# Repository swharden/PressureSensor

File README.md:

# Digital Pressure Sensor

This project contains design files for a minimal complexity digital pressure sensor. It uses a [HX710](https://image.micros.com.pl/_dane_techniczne_auto/uphx710b%20smd.pdf) 24-bit ADC to read differential voltage across a Whetstone bridge pressure sensor, then an [AD64DD32](https://ww1.microchip.com/downloads/aemDocuments/documents/MCU08/ProductDocuments/DataSheets/AVR64DD32-28-Prelim-DataSheet-DS40002315B.pdf) applies signal filtering in software and outputs the result as an analog signal using its built-in DAC. Filtering in software allows filter settings and recording modes to be adjusted in real time or further modified using firmware updates. Pressure is displayed on a multiplexed 7-segment display driven directly by pins of the microcontroller. Display mode can be toggled between pressure value, wave period, or wave frequency.

### Version 1.0

### Version 2.0

#### Build Notes

* Through-hole buttons have leads out the bottom which fight against adhesive pads at the corners
* PCB near display could be notched to facilitate string or zip tie mounting vertically
* I'm unsure whether I like the USB connector on the bottom. The whole board could be turned upside down with the connector and buttons on the top.

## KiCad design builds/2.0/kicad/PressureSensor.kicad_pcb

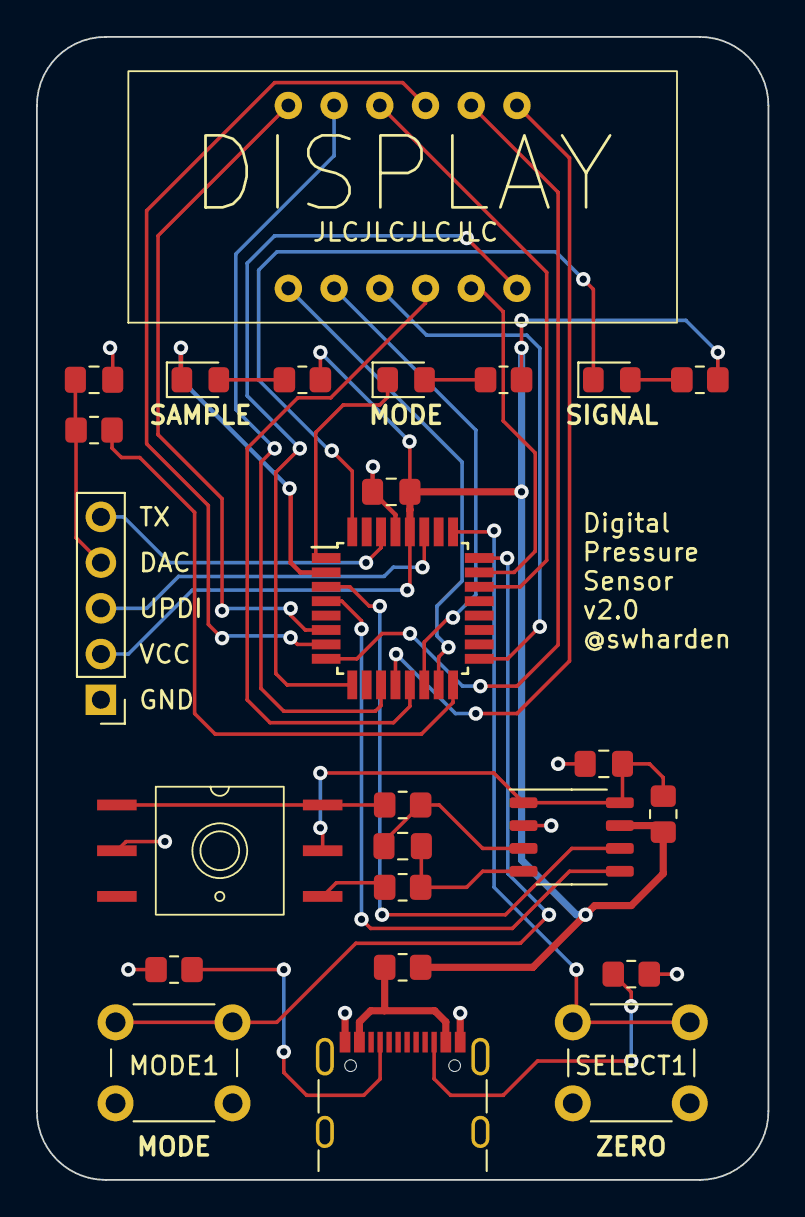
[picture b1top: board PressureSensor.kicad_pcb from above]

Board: 2 copper layers, 40.6 x 63.5 mm, 25 parts (0 on the bottom side), 36 nets.

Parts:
C1, C2, C3, C4: .1u; C_0805_2012Metric_Pad1.18x1.45mm_HandSolder
D1: SAMPLE; LED_0805_2012Metric_Pad1.15x1.40mm_HandSolder
D2: MODE; LED_0805_2012Metric_Pad1.15x1.40mm_HandSolder
D3: STATUS; LED_0805_2012Metric_Pad1.15x1.40mm_HandSolder
FB1, FB2: FerriteBead_Small; R_0805_2012Metric_Pad1.20x1.40mm_HandSolder
J1: USB_C_Receptacle_PowerOnly_6P; USB_C_Receptacle_GCT_USB4105-xx-A_16P_TopMnt_Horizontal
J2: PROG; PinHeader_1x05_P2.54mm_Vertical
MODE1: SW_Push; SW_PUSH_6mm_H5mm
R1, R2: 5.7k; R_0805_2012Metric_Pad1.20x1.40mm_HandSolder
R3, R4, R8: 1k; R_0805_2012Metric_Pad1.20x1.40mm_HandSolder
R5, R6, R7: 100k; R_0805_2012Metric_Pad1.20x1.40mm_HandSolder
SELECT1: SW_Push; SW_PUSH_6mm_H5mm
U1: SENSOR; pressure-sensor-SOIC-6
U2: HX710; SSOP-8_3.9x5.05mm_P1.27mm
U3: DISPLAY; 7_seg_display_DIP12
U4: AVR64DD32; TQFP-32_7x7mm_P0.8mm

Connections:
AVCC: C2.1, FB2.1, U1.5 (VCC), U2.1 (VREF), U2.8 (AVCC)
BTN1: MODE1.1, U4.24 (PF4)
BTN2: SELECT1.1, U4.25 (PF5)
DAC: C4.1, J2.4, R8.1
DIG_1: U3.12 (DIG_1), U4.6 (PC0)
DIG_2: U3.9 (DIG_2), U4.7 (PC1)
DIG_3: U3.8 (DIG_3), U4.8 (PC2)
DIG_4: U3.6 (DIG_4), U4.9 (PC3)
GND: C2.2, C3.2, C4.2, J1.A1, J1.A12 (GND), J2.1, MODE1.2, R1.2, R2.1, SELECT1.2, U1.2 (GND), U2.2 (GND), U4.29 (GND)
LED1: D1.1 (K), U4.32 (PA2)
LED2: D2.1 (K), U4.1 (PA3)
LED3: D3.1 (K), U4.2 (PA4)
MCU_DAC: R8.2, U4.16 (PD6)
unnamed: D1.2 (A), R5.1
unnamed: D2.2 (A), R6.1
unnamed: D3.2 (A), R7.1
unnamed: FB1.1, J1.A4, J1.A9 (VBUS)
unnamed: J1.A5 (CC1), R1.1
unnamed: J1.B5 (CC2), R2.2
unnamed: R3.1, U1.1 (V-), U1.6 (V-)
unnamed: R4.2, U1.4 (Vpos)
unnamed: C1.1, R3.2, U2.3 (IN_NEG)
unnamed: C1.2, R4.1, U2.4 (IN_POS)
SEG_A: U3.11 (SEG_A), U4.11 (PD1)
SEG_B: U3.7 (SEG_B), U4.12 (PD2)
SEG_C: U3.4 (SEG_C), U4.13 (PD3)
SEG_D: U3.2 (SEG_D), U4.14 (PD4)
SEG_E: U3.1 (SEG_E), U4.15 (PD5)
SEG_F: U3.10 (SEG_F), U4.22 (PF2)
SEG_G: U3.5 (SEG_G), U4.23 (PF3)
SEG_P: U3.3 (SEG_P), U4.17 (VREFA/PD7)
SPI_CLK: U2.5 (SCK), U4.4 (PA6)
SPI_MISO: U2.6 (OUT), U4.3 (PA5)
TX: J2.5, U4.30 (XTALHF1/PA0)
UPDI: J2.3, U4.27 (UPDI)
VCC: C3.1, FB1.2, FB2.2, J2.2, R5.2, R6.2, R7.2, U2.7 (DVCC), U4.28 (VDD)

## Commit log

2023-09-07 start pcb
2023-09-10 pressure sensor footprint
2023-09-10 custom footprints
2023-09-10 schematic: improve filtering
2023-09-10 schematic: all major components
2023-09-10 improve HX710 symbol
2023-09-10 update PCB layout
2023-09-10 kicad/ → builds/1.0/
2023-09-10 update gerbers
    move drill holes under display
2023-09-19 build 1.0 readme
2023-09-19 build 1.0 software
2023-09-20 fix startup LED state
2023-09-22 update software
2023-09-22 2.0: new schematic
2023-09-30 update libraries
2023-09-30 layout PCB
2023-10-01 update PCB
2023-10-11 2.0 software
2023-10-11 2.0 software: invert screen
